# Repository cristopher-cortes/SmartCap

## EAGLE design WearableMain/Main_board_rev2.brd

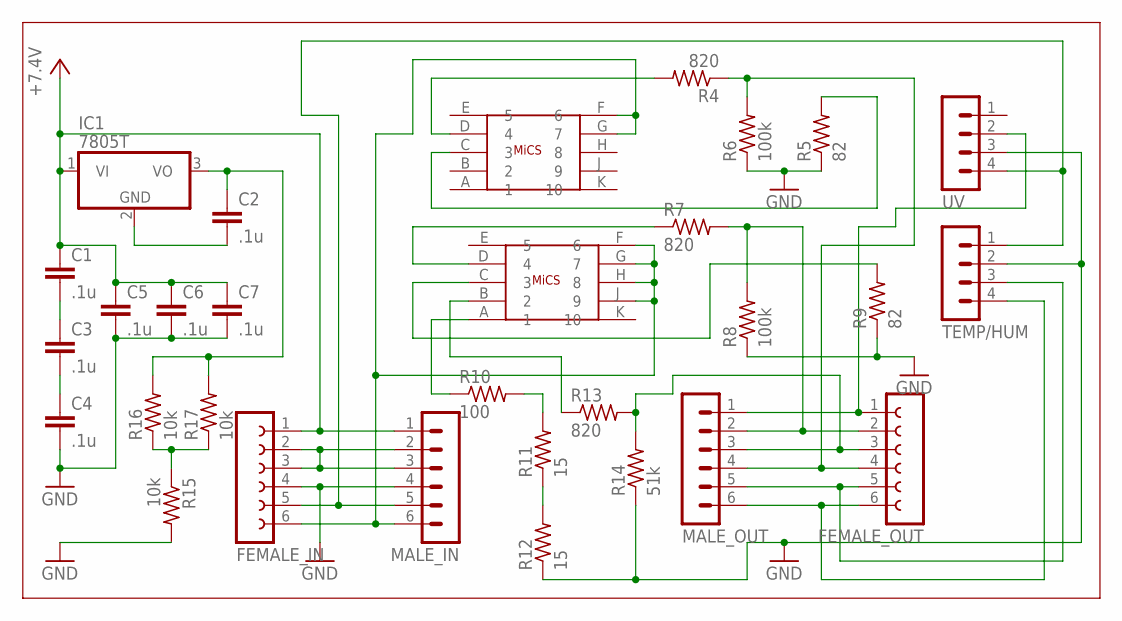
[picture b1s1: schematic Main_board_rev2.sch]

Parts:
2614, 4514: MICS_SMD; MICS_SOCKET
C1, C2, C3, C4, C5, C6, C7: .1u; C2.5-3
FEMALE_IN: FE06W
FEMALE_OUT: FE06W
IC1: 7805T; TO220H
MALE_IN: MA06-1
MALE_OUT: MA06-1
R4, R7, R13: 820; 0204/7
R5, R9: 82; 0204/7
R6, R8: 100k; 0204/7
R10: 100; 0204/7
R11, R12: 15; 0204/7
R14: 51k; 0204/7
R15, R16, R17: 10k; 0204/7
TEMP/HUM: MA04-1
UV: MA04-1

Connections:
+5V: C1.1, C5.1, C6.1, C7.1, FEMALE_IN.1, IC1.1 (VI), MALE_IN.1
GND: C4.2, C5.2, C6.2, C7.2, FEMALE_IN.4, MALE_IN.4, R5.1, R6.1, R8.1, R9.1, R12.1, R14.1, R15.2, TEMP/HUM.2, UV.3
unnamed: C2.1, IC1.3 (VO), R16.2, R17.2
unnamed: C2.2, IC1.2 (GND)
unnamed: R15.1, R16.1, R17.1
unnamed: C3.2, C4.1
unnamed: C1.2, C3.1
unnamed: FEMALE_OUT.4, MALE_OUT.4, R4.1, R6.2
unnamed: 2614.C (3), R5.2
unnamed: FEMALE_IN.2, FEMALE_IN.3, MALE_IN.2, MALE_IN.3
unnamed: 2614.D (4), R4.2
unnamed: FEMALE_OUT.2, MALE_OUT.2, R7.2, R8.2
unnamed: 4514.C (3), R9.2
unnamed: 4514.D (4), R7.1
unnamed: R10.2, R11.2
unnamed: R11.1, R12.2
unnamed: 4514.A (1), R10.1
unnamed: FEMALE_OUT.3, MALE_OUT.3, R13.2, R14.2
unnamed: 4514.B (2), R13.1
unnamed: FEMALE_OUT.1, MALE_OUT.1, UV.2
unnamed: FEMALE_IN.5, MALE_IN.5, TEMP/HUM.1, UV.4
unnamed: 2614.F (6), 2614.G (7), 4514.F (6), 4514.G (7), 4514.H (8), 4514.J (9), FEMALE_IN.6, MALE_IN.6
unnamed: FEMALE_OUT.5, MALE_OUT.5, TEMP/HUM.3
unnamed: FEMALE_OUT.6, MALE_OUT.6, TEMP/HUM.4

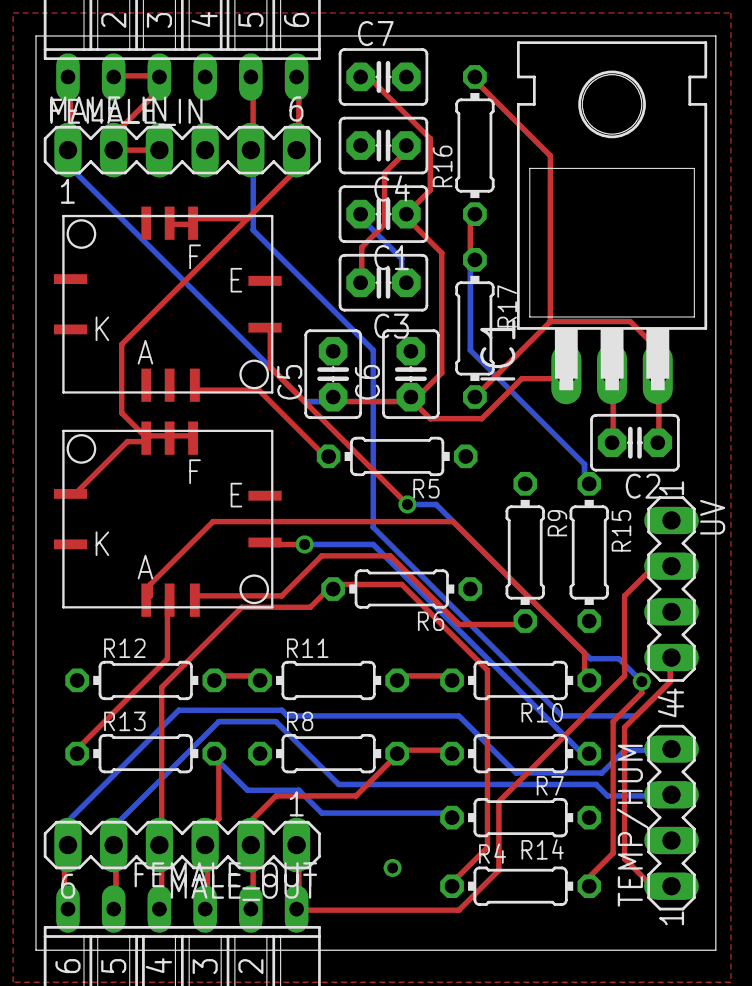
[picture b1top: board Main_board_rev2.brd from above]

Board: 2 copper layers, 37.8 x 50.8 mm, 30 parts (0 on the bottom side), 24 nets.

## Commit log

2015-08-23 2nd Commit
2015-08-24 3rd Commit
